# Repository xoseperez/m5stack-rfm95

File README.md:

# M5Stack TTN Node

This is a LoRaWAN node based on the great M5Stack development platform.
It uses a RFM95 by HopeRF and the standard LMIC stack.
The sample code is configured to connect to The Things Network using EU frequency, but you can easily change that.

This repository contains:

* PCB schematics, layout (for Eagle) and gerbers.
* 3D model of different enclosure options (bottom layer, middle layer), both OpenSCAD and STL files.
* Sample code that sends an auto-increment number and sleeps the board.

## License

Copyright (C) 2018 by Xose Pérez (@xoseperez)

This program is free software: you can redistribute it and/or modify
it under the terms of the GNU General Public License as published by
the Free Software Foundation, either version 3 of the License, or
(at your option) any later version.

This program is distributed in the hope that it will be useful,
but WITHOUT ANY WARRANTY; without even the implied warranty of
MERCHANTABILITY or FITNESS FOR A PARTICULAR PURPOSE.  See the
GNU General Public License for more details.

You should have received a copy of the GNU General Public License
along with this program.  If not, see <http://www.gnu.org/licenses/>.

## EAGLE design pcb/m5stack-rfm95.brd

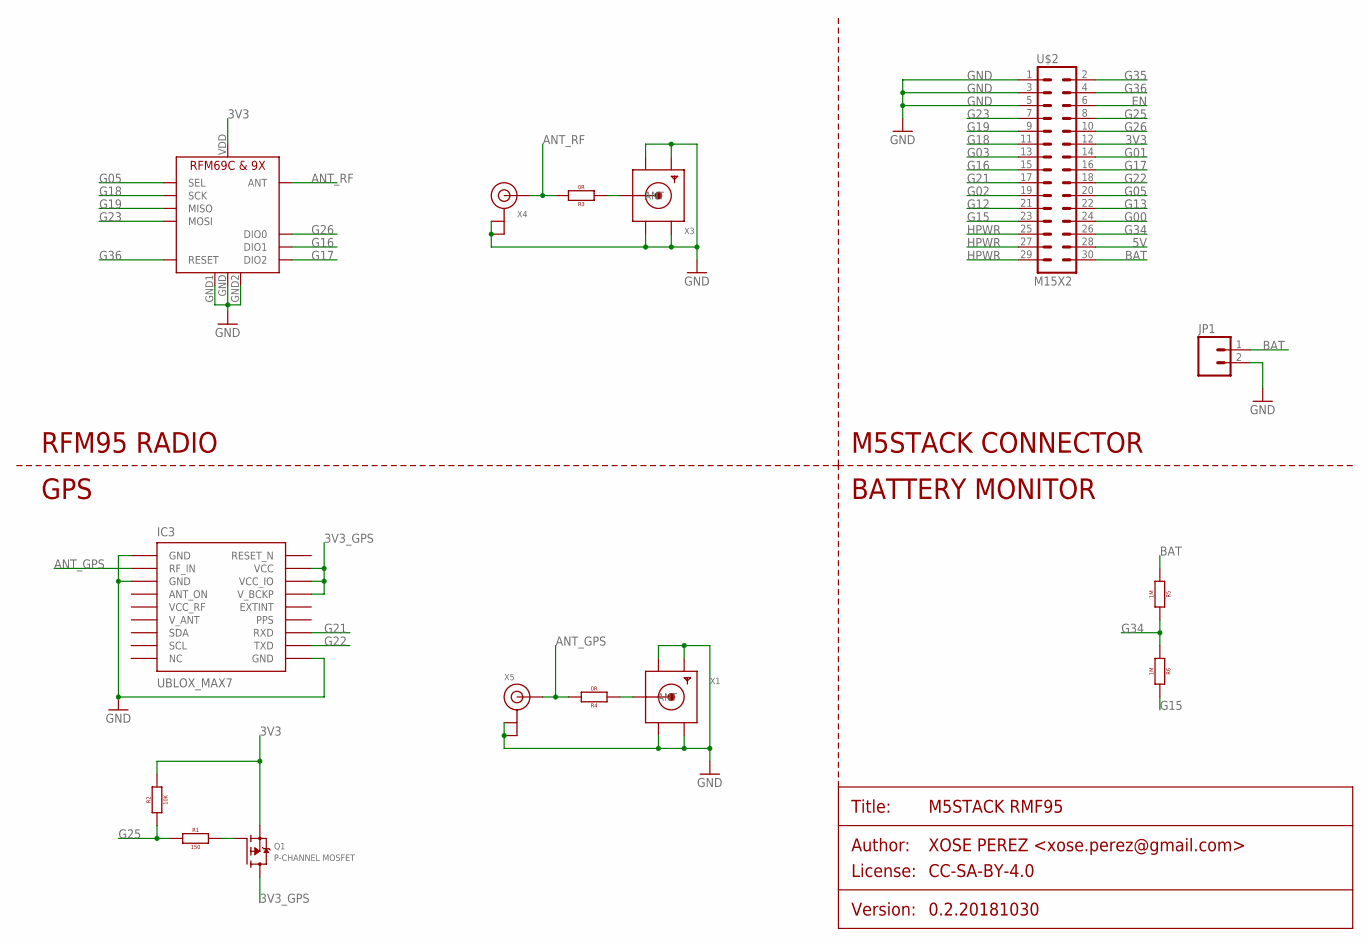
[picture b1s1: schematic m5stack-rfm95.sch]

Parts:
IC1: RFM69HCW-RFM95; RFM69HCW-RFM95-MINPADS
IC3: UBLOX_MAX7
JP1: M02-JST-2MM-SMT; JST-2-SMD
Q1: P-CHANNEL MOSFET; SOT23-R
R1: 150; 0805
R2: 10K; 0805
R3, R4: 0R; 0805
R5, R6: 1M; 0805
U$2: M15X2; 2X15
X1, X3: SMACONNECTOR; SMA90_DIP
X4, X5: ANTENNA_U.FL; U.FL

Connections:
3V3: IC1.VDD (VCC), Q1.2 (S), R2.2, U$2.12
3V3_GPS: IC3.P$6 (V_BCKP), IC3.P$7 (VCC_IO), IC3.P$8 (VCC), Q1.3 (D)
5V: U$2.28
ANT_GPS: IC3.P$11 (RF_IN), R4.2, X5.3 (SIGNAL)
ANT_RF: IC1.ANT, R3.2, X4.3 (SIGNAL)
BAT: JP1.1 (2), R5.1, U$2.30
EN: U$2.6
G00: U$2.24
G01: U$2.14
G02: U$2.19
G03: U$2.13
G05: IC1.NSS (SEL), U$2.20
G12: U$2.21
G13: U$2.22
G15: R6.2, U$2.23
G16: IC1.DIO1, U$2.15
G17: IC1.DIO2, U$2.16
G18: IC1.SCK, U$2.11
G19: IC1.MISO, U$2.9
G21: IC3.P$3 (RXD), U$2.17
G22: IC3.P$2 (TXD), U$2.18
G23: IC1.MOSI, U$2.7
G25: R1.1, R2.1, U$2.8
G26: IC1.DIO0, U$2.10
G34: R5.2, R6.1, U$2.26
G35: U$2.2
G36: IC1.RESET, U$2.4
GND: IC1.GND, IC1.GND1, IC1.GND2, IC3.P$1 (GND), IC3.P$10 (GND), IC3.P$12 (GND), JP1.2 (1), U$2.1, U$2.3, U$2.5, X1.GND1, X1.GND2, X1.GND3, X1.GND4, X3.GND1, X3.GND2, X3.GND3, X3.GND4, X4.1 (GND), X4.2 (GND), X5.1 (GND), X5.2 (GND)
HPWR: U$2.25, U$2.27, U$2.29
unnamed: R4.1, X1.ANTENNA (ANT)
unnamed: R3.1, X3.ANTENNA (ANT)
unnamed: Q1.1 (G), R1.2
VCC_RF: IC3.P$14 (VCC_RF)
V_ANT: IC3.P$15 (V_ANT)

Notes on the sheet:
RFM95 RADIO
M5STACK CONNECTOR
GPS
BATTERY MONITOR

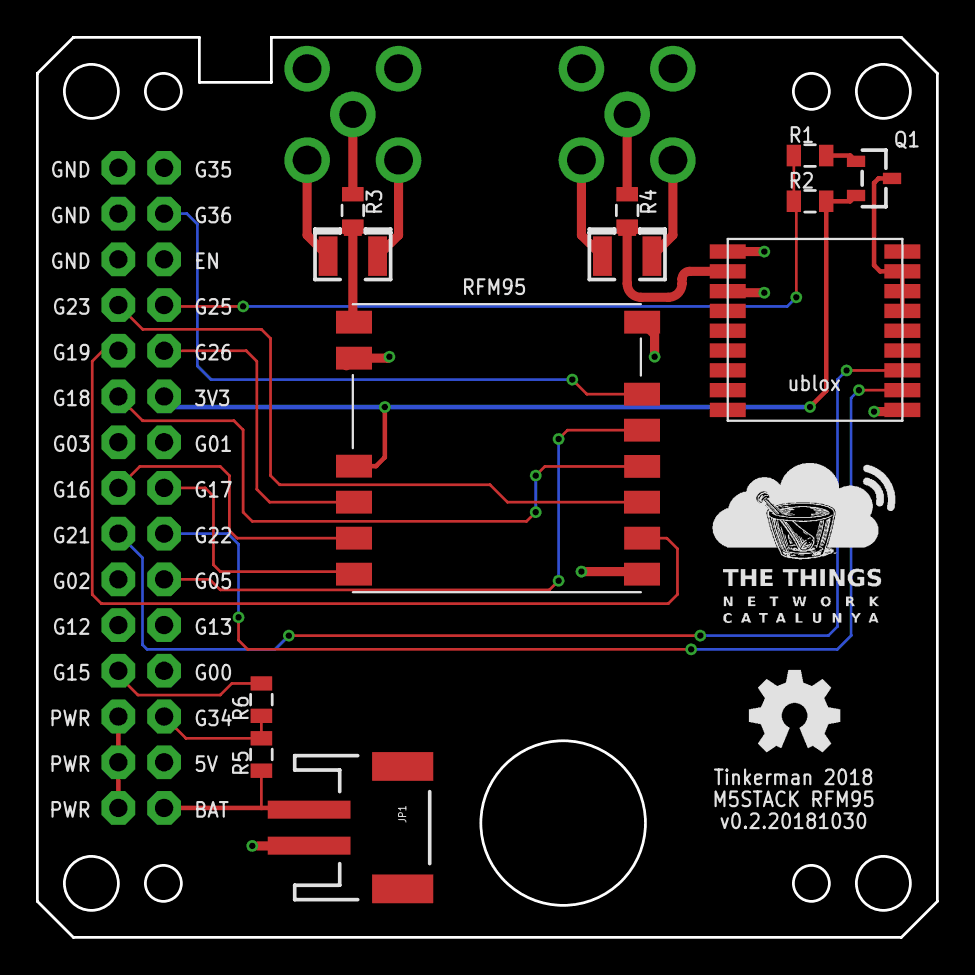
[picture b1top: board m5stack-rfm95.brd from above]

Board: 2 copper layers, 50.0 x 50.0 mm, 15 parts (0 on the bottom side), 23 nets.

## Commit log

2018-06-09 Fix .gitignore
2018-06-09 Fix sleep on battery, added logo
2018-06-09 Fix credentials for travis
2018-06-10 Moved to MCCI LMIC implementation
2018-06-10 PCB and 3D printed models images
2018-06-10 Cleanup bin2code file
2018-06-10 Inline documentation of the sleep process
2018-09-30 Small rework
2018-09-30 Keep uplink counter across sleeps
2018-11-14 Clean code and send ping every 15s
2021-02-07 MOdified enclosure
2021-02-07 Changes in the PCB
2021-02-07 Added BT GPS
2021-02-07 Option to disable GPS code, disabled by default for backwards compatibility

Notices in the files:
pcb/m5stack-rfm95.sch:
PROJECT_LICENSE: CC-SA-BY-4.0
